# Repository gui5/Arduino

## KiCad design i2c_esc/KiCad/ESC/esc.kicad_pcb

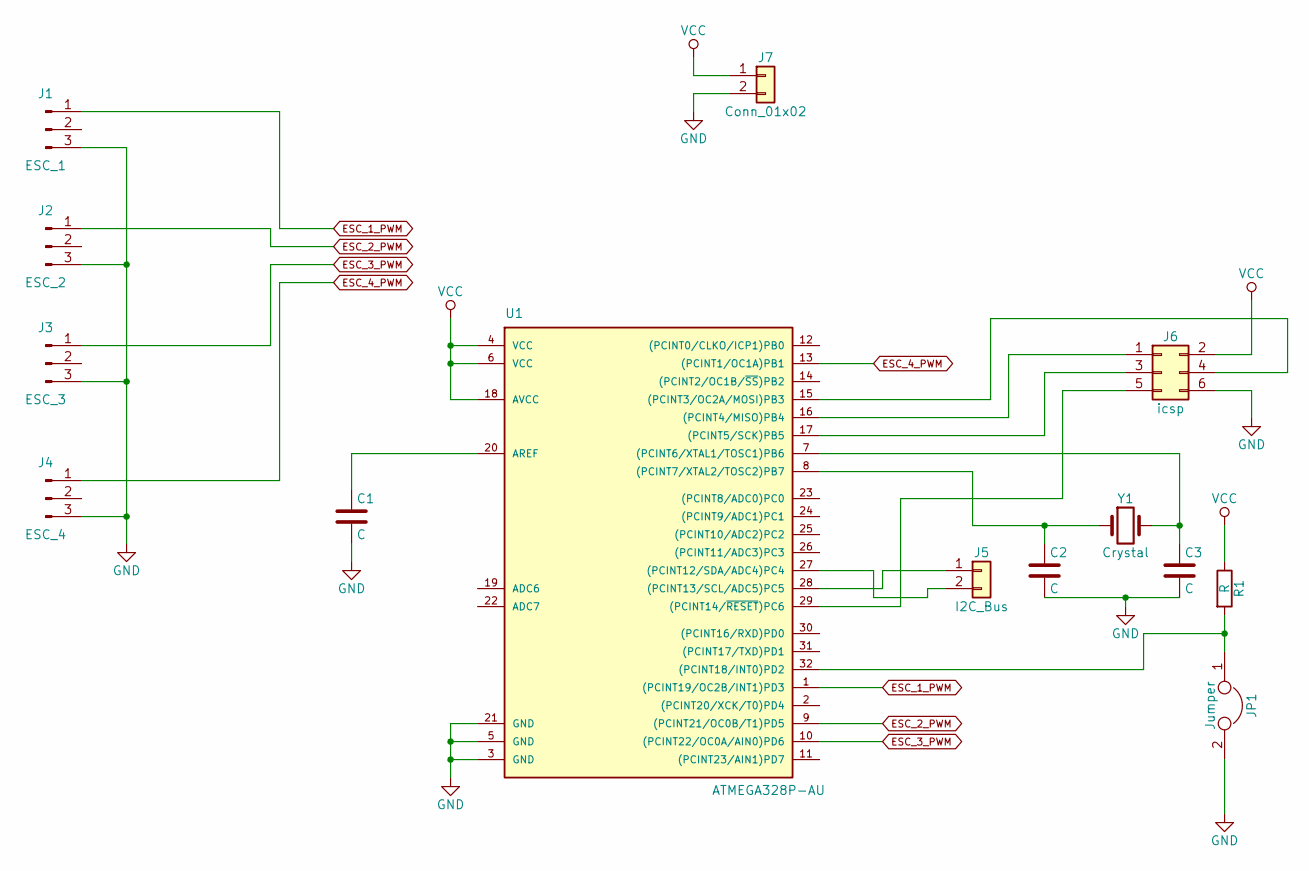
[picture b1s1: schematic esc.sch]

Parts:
C1, C2, C3: C; C_0603
J1: ESC_1; Pin_Header_Angled_1x03_Pitch2.00mm
J2: ESC_2; Pin_Header_Angled_1x03_Pitch2.00mm
J3: ESC_3; Pin_Header_Angled_1x03_Pitch2.00mm
J4: ESC_4; Pin_Header_Angled_1x03_Pitch2.00mm
J5: I2C_Bus; Pin_Header_Angled_1x02_Pitch2.00mm
J6: icsp; Pin_Header_Straight_2x03_Pitch2.00mm
J7: Conn_01x02; Pin_Header_Angled_1x02_Pitch2.00mm
JP1: Jumper; Pin_Header_Straight_1x02_Pitch2.00mm
R1: R; R_0805
U1: ATMEGA328P-AU; TQFP-32_7x7mm_Pitch0.8mm
Y1: Crystal; Crystal_SMD_HC49-SD

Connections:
ESC_1_PWM: J1.1, U1.1 ((PCINT19/OC2B/INT1)PD3)
ESC_2_PWM: J2.1, U1.9 ((PCINT21/OC0B/T1)PD5)
ESC_3_PWM: J3.1, U1.10 ((PCINT22/OC0A/AIN0)PD6)
ESC_4_PWM: J4.1, U1.13 ((PCINT1/OC1A)PB1)
GND: C1.2, C2.2, C3.2, J1.3, J2.3, J3.3, J4.3, J6.6, J7.2, JP1.2, U1.3 (GND), U1.5 (GND), U1.21 (GND)
unnamed: C1.1, U1.20 (AREF)
unnamed: C2.1, U1.8 ((PCINT7/XTAL2/TOSC2)PB7), Y1.1
unnamed: C3.1, U1.7 ((PCINT6/XTAL1/TOSC1)PB6), Y1.2
unnamed: J5.1, U1.28 ((PCINT13/SCL/ADC5)PC5)
unnamed: J5.2, U1.27 ((PCINT12/SDA/ADC4)PC4)
unnamed: J6.1, U1.16 ((PCINT4/MISO)PB4)
unnamed: J6.3, U1.17 ((PCINT5/SCK)PB5)
unnamed: J6.4, U1.15 ((PCINT3/OC2A/MOSI)PB3)
unnamed: J6.5, U1.29 ((PCINT14/~RESET~)PC6)
unnamed: JP1.1, R1.2, U1.32 ((PCINT18/INT0)PD2)
VCC: J6.2, J7.1, R1.1, U1.4 (VCC), U1.6 (VCC), U1.18 (AVCC)

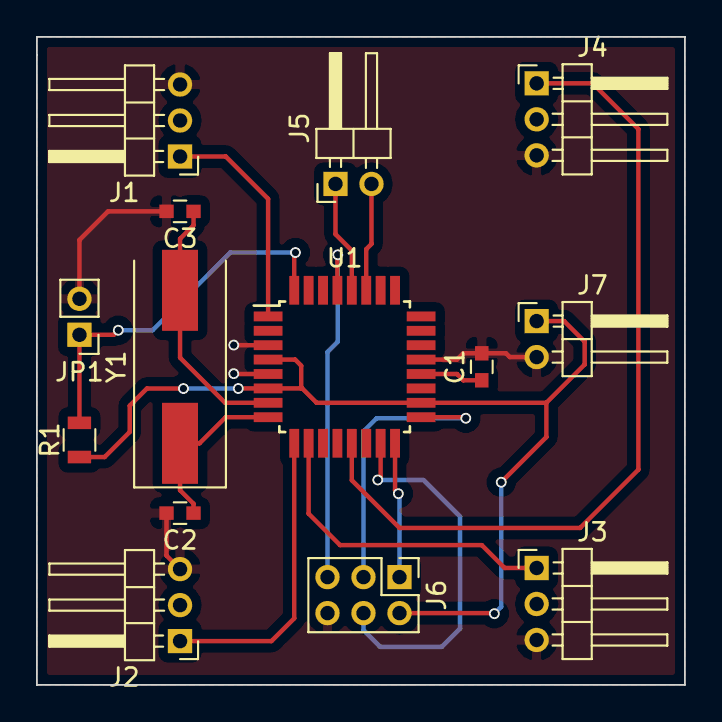
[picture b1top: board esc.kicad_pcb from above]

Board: 2 copper layers, 36.0 x 36.0 mm, 14 parts (0 on the bottom side), 16 nets.

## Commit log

2017-12-28 1 commit
2017-12-28 Changes to be committed: new file: i2c_esc/.vscode/arduino.json new file: i2c_esc/.vscode/c_cpp_properties.json new file: i2c_esc/esc.ino new file: i2c_gps/.vscode/arduino.json new file: i2c_gps/.vsc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
2017-12-28 Added board project
2017-12-28 arduino configured
2018-01-19 pcb update
